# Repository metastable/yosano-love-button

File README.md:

# yosano-love-button
Field hack YOSANO - oryza -  ♥yosano button

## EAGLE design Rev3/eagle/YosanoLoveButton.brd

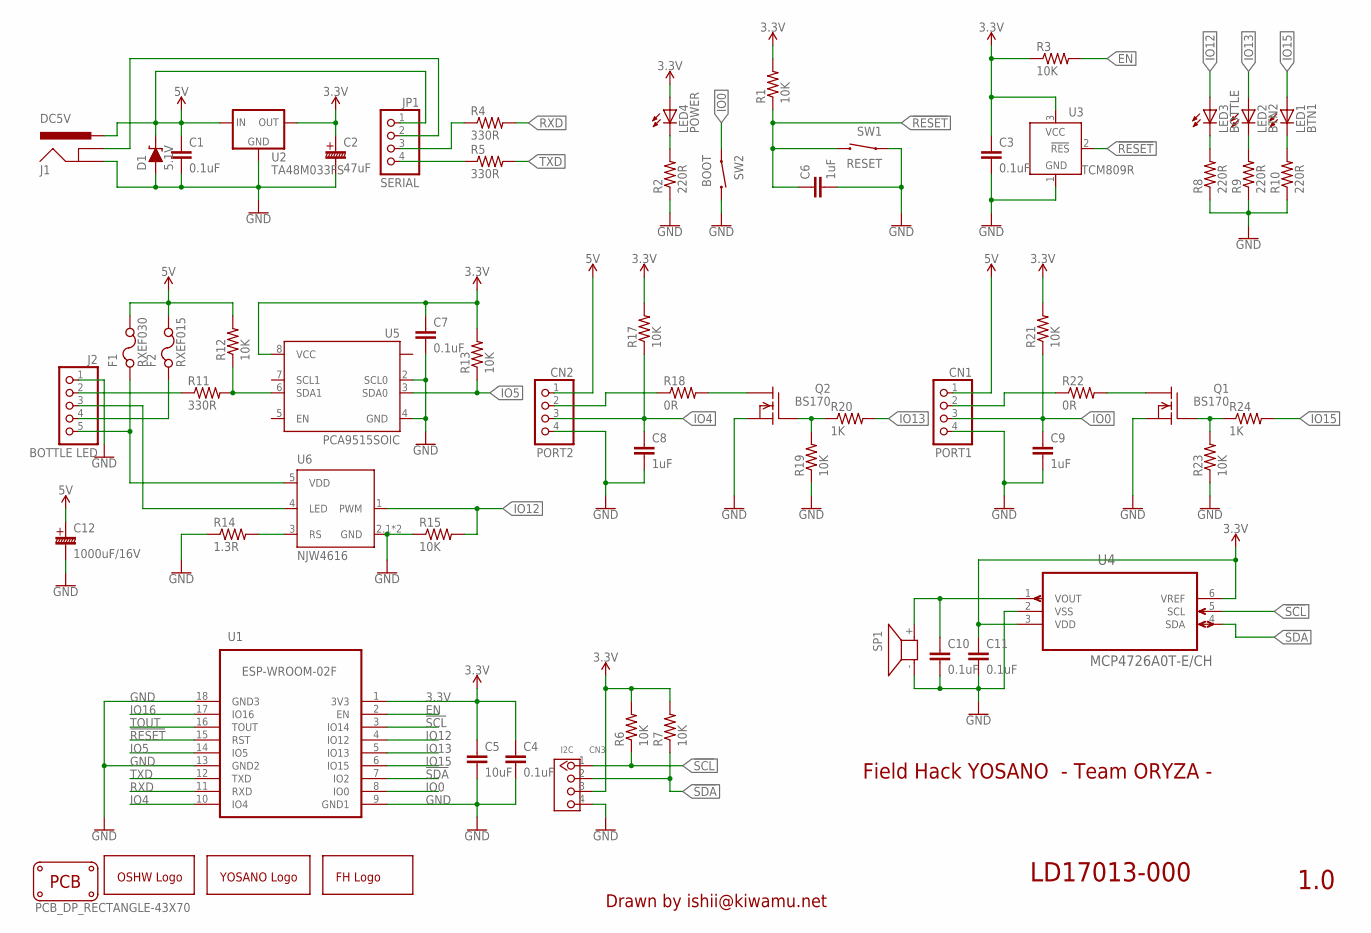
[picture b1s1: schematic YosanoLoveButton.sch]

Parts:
C1, C3, C4, C7: 0.1uF; C5B2.5
C2: 47uF; E2,0-5
C5: 10uF; C5B2.5
C6, C8, C9: 1uF; C5B2.5
C10, C11: 0.1uF; C5B2.5; MPN RDER72E104K2K1H03B
C12: 1000uF/16V; E5,0-10
CN1: PORT1; B4B-XH
CN2: PORT2; B4B-XH
CN3: I2C; HW4-2.0
D1: 5.1V; ZDIO-5-LD
F1: RXEF030; PTC-PTH
F2: RXEF015; PTC-PTH
GOLD_ORB_SM1: OSHWLOGOLOGO5MM; OSHW_5MM
J1: DC5V; POWER_JACK_PTH
J2: BOTTLE LED; MD-50SM
JP1: SERIAL; 1X04
LED1: BTN1; LED3MM
LED2: BTN2; LED3MM
LED3: BOTTLE; LED3MM
LED4: POWER; LED3MM
PCB1: PCB_DP_RECTANGLE-43X70; DP7043_V1
Q1, Q2: BS170; TO92
R1, R3, R6, R7, R12, R13, R15, R17, R19, R21, R23: 10K; 0204/5
R2, R8, R9, R10: 220R; 0204/5
R4, R5, R11: 330R; 0204/5
R14: 1.3R; 0204/5
R18, R22: 0R; 0204/5
R20, R24: 1K; 0204/5
SP1: PKM13EPYH4000
SW1: RESET; TVBP06
SW2: BOOT; TVBP06
U1: ESP-WROOM-02F; FRONT-FACE
U2: TA48M033FS; HSIP3
U3: TCM809R; SOT23B-3
U4: MCP4726A0T-E/CH; SOT95P270X145-6N
U5: PCA9515SOIC; SO08
U6: NJW4616; SOT-89-5
U$1: YOSANOLOGO; YOSANOCHO
U$2: FHLOGO; FIELDHACK-YOSANO

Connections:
3.3V: C2.+, C3.1, C4.1, C5.1, C7.1, C11.1, CN3.3, LED4.A, R1.2, R3.1, R6.2, R7.2, R13.2, R17.2, R21.2, U1.1 (3V3), U2.P$2 (OUT), U3.3 (VCC), U4.3 (VDD), U4.6 (VREF), U5.8 (VCC)
5V: C1.1, C12.+, CN1.1, CN2.1, D1.C, F1.2, F2.2, J1.PWR, JP1.1, R12.2, U2.P$1 (IN)
!RESET: C6.1, R1.1, SW1.2, U1.15 (RST), U3.2 (!RES)
!SCL: CN3.1, R6.1, U1.3 (IO14), U4.5 (SCL)
!SDA: CN3.2, R7.1, U1.7 (IO2), U4.4 (SDA)
EN: R3.2, U1.2 (EN)
GND: C1.2, C2.-, C3.2, C4.2, C5.2, C6.2, C7.2, C8.2, C9.2, C10.2, C11.2, C12.-, CN1.4, CN2.4, CN3.4, D1.A, J1.GND, J2.1, Q1.1 (S), Q2.1 (S), R2.1, R8.1, R9.1, R10.1, R14.1, R15.1, R19.1, R23.1, SP1.- (2), SW1.1, SW2.2, U1.9 (GND1), U1.13 (GND2), U1.18 (GND3), U2.P$3 (GND), U3.1 (GND), U4.2 (VSS), U5.2 (SCL0), U5.4 (GND), U6.2.1 (GND), U6.2.2 (GND)
IO0: C9.1, CN1.3, R21.1, SW2.1, U1.8 (IO0)
IO4: C8.1, CN2.3, R17.1, U1.10 (IO4)
IO5: R13.1, U1.14 (IO5), U5.3 (SDA0)
IO12: LED3.A, R15.2, U1.4 (IO12), U6.1 (PWM)
IO13: LED2.A, R20.2, U1.5 (IO13)
IO15: LED1.A, R24.2, U1.6 (IO15)
IO16: U1.17 (IO16)
unnamed: LED3.K (C), R8.2
unnamed: LED4.K (C), R2.2
unnamed: JP1.4, R5.1
unnamed: R14.2, U6.3 (RS)
unnamed: JP1.3, R4.1
unnamed: LED2.K (C), R9.2
unnamed: LED1.K (C), R10.2
unnamed: F1.1, J2.5, U6.5 (VDD)
unnamed: J2.3, U6.4 (LED)
unnamed: J1.GNDBREAK, JP1.2
unnamed: Q2.3 (D), R18.2
unnamed: J2.2, R11.1
unnamed: CN2.2, R18.1
unnamed: Q2.2 (G), R19.2, R20.1
unnamed: Q1.3 (D), R22.2
unnamed: C10.1, SP1.+ (1), U4.1 (VOUT)
unnamed: F2.1, J2.4
unnamed: Q1.2 (G), R23.2, R24.1
unnamed: CN1.2, R22.1
unnamed: R11.2, R12.1, U5.6 (SDA1)
RXD: R4.2, U1.11 (RXD)
TOUT: U1.16 (TOUT)
TXD: R5.2, U1.12 (TXD)

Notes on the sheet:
Field Hack YOSANO - Team ORYZA -
LD17013-000
Drawn by ishii@kiwamu.net
1.0

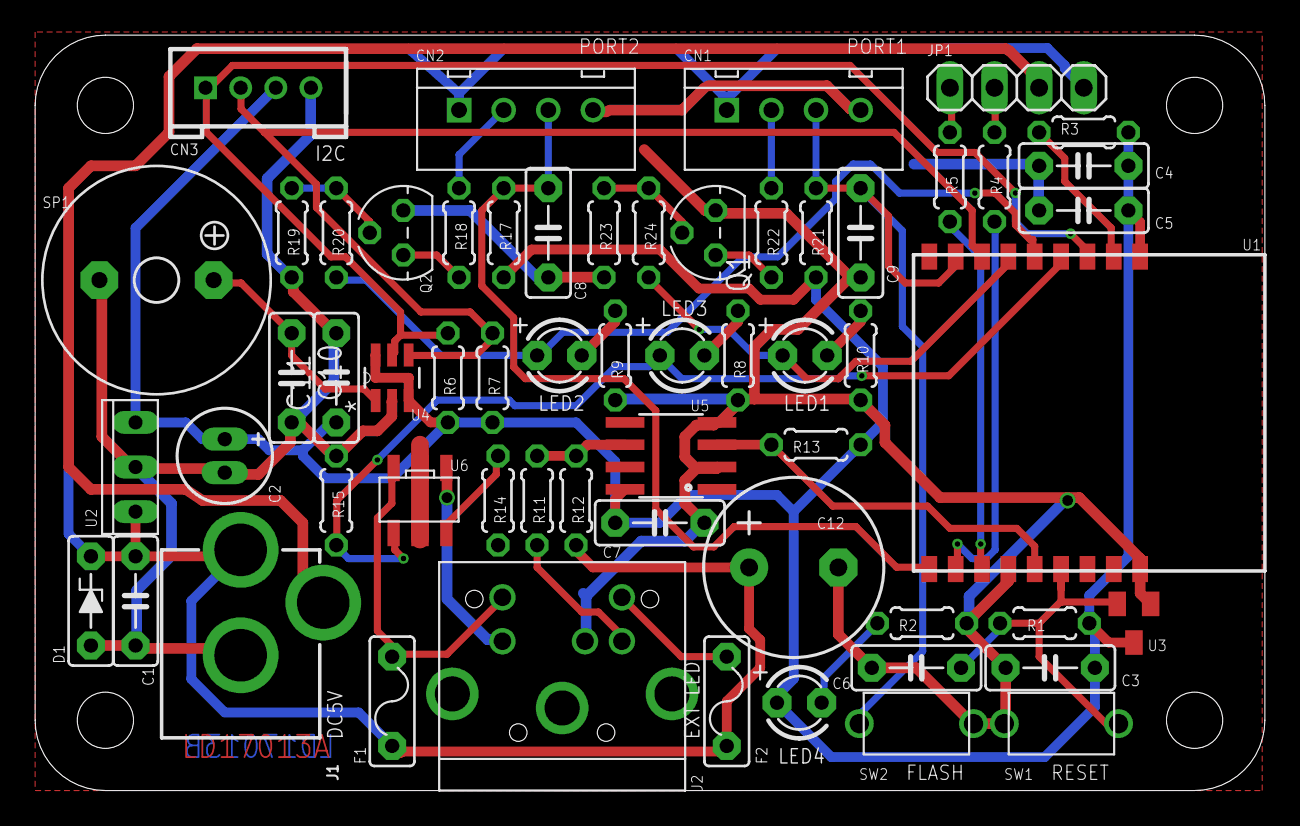
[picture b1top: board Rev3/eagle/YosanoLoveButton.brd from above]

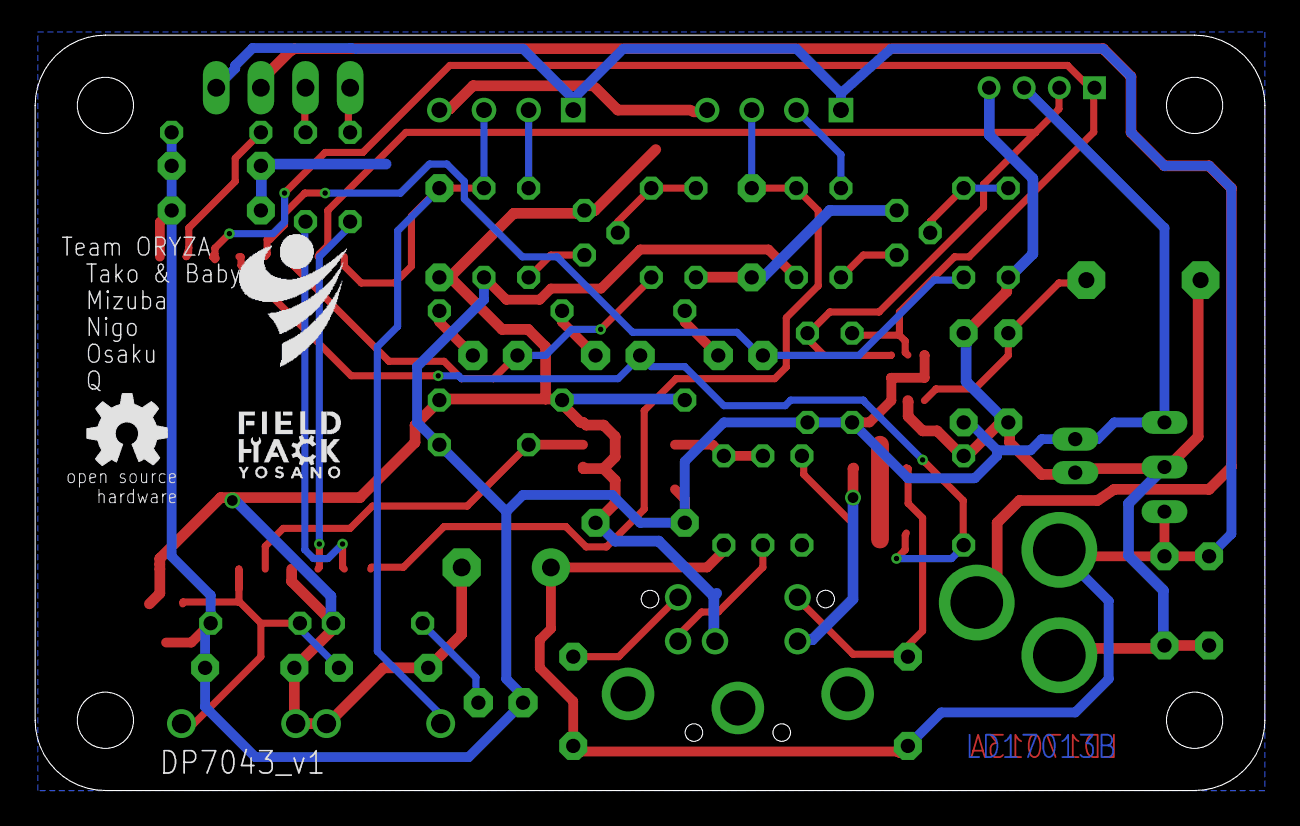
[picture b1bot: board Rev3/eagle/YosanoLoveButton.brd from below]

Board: 2 copper layers, 70.0 x 43.0 mm, 63 parts (3 on the bottom side), 35 nets.

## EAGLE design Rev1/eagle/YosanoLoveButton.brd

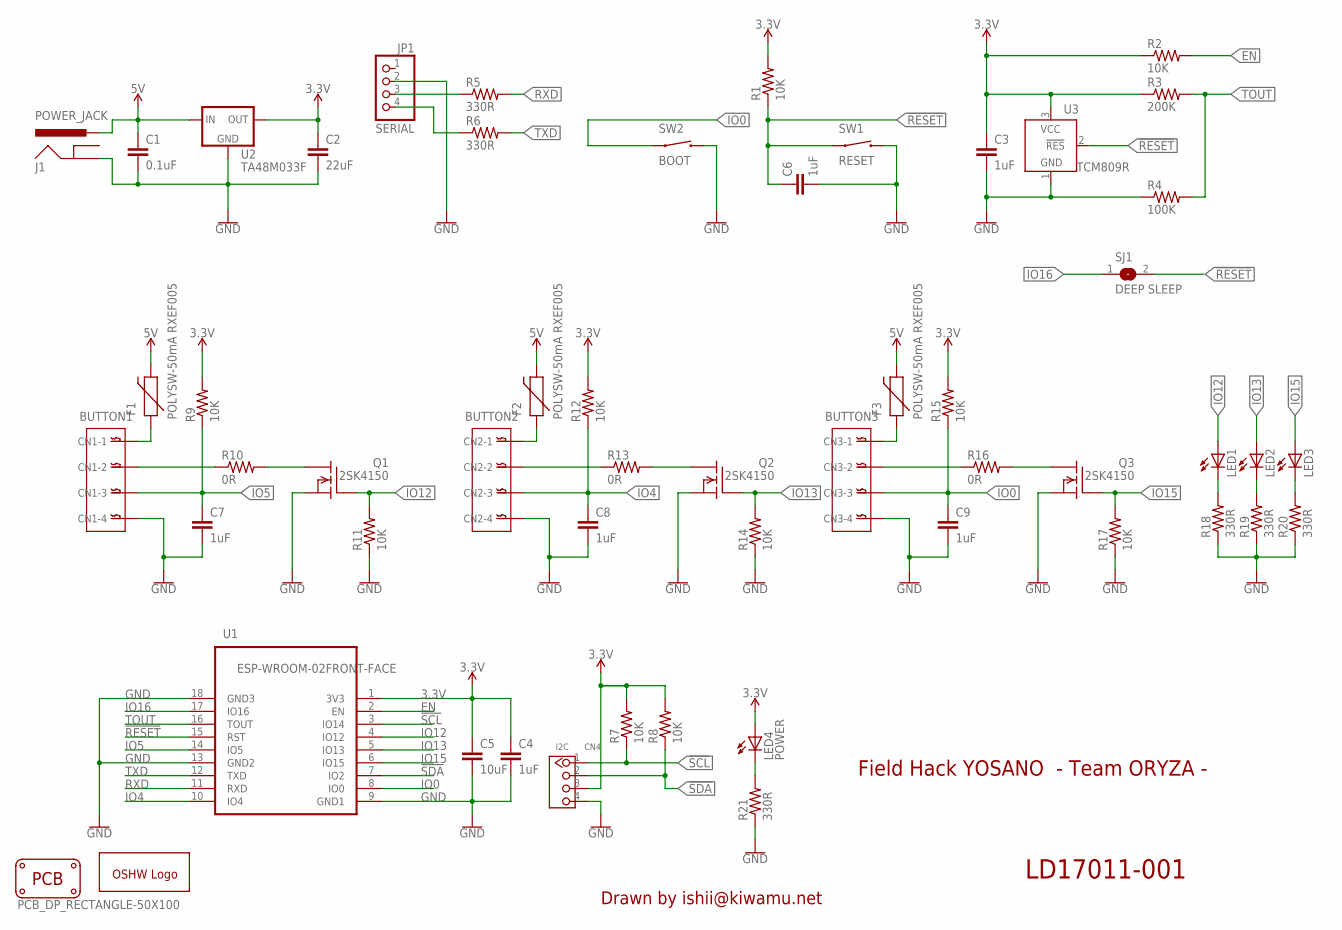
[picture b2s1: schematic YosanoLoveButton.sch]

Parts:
C1: 0.1uF; C5B2.5
C2: 22uF; C5B2.5
C3, C4, C6, C7, C8, C9: 1uF; C5B2.5
C5: 10uF; C5B2.5
CN1: BUTTON1; B4B-XH
CN2: BUTTON2; B4B-XH
CN3: BUTTON3; B4B-XH
CN4: I2C; HW4-2.0
F1, F2, F3: POLYSW-50mA RXEF005; PTC
GOLD_ORB_SM1: OSHWLOGOLOGO5MM; OSHW_5MM
J1: POWER_JACK; POWER_JACK_PTH
JP1: SERIAL; 1X04
LED1, LED2, LED3: LED3MM
LED4: POWER; LED3MM
PCB1: PCB_DP_RECTANGLE-50X100; DP10050_V1
Q1, Q2, Q3: 2SK4150; TO92
R1, R2, R7, R8, R9, R11, R12, R14, R15, R17: 10K; 0204/7
R3: 200K; 0204/7
R4: 100K; 0204/7
R5, R6, R18, R19, R20, R21: 330R; 0204/7
R10, R13, R16: 0R; 0204/7
SJ1: DEEP SLEEP; SOLDERJUMPER_REFLOW
SW1: RESET; TVBP06
SW2: BOOT; TVBP06
U1: ESP-WROOM-02FRONT-FACE; FRONT-FACE
U2: TA48M033F; DPACK
U3: TCM809R; SOT23B-3

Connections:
3.3V: C2.1, C3.1, C4.1, C5.1, CN4.3, LED4.A, R1.2, R2.1, R3.1, R7.2, R8.2, R9.2, R12.2, R15.2, U1.1 (3V3), U2.3 (OUT), U3.3 (VCC)
5V: C1.1, F1.P$2 (2), F2.P$2 (2), F3.P$2 (2), J1.PWR, U2.1 (IN)
!RESET: C6.1, R1.1, SJ1.2, SW1.1, U1.15 (RST), U3.2 (!RES)
!SCL: CN4.1, R7.1, U1.3 (IO14)
!SDA: CN4.2, R8.1, U1.7 (IO2)
EN: R2.2, U1.2 (EN)
GND: C1.2, C2.2, C3.2, C4.2, C5.2, C6.2, C7.2, C8.2, C9.2, CN1.P$4, CN2.P$4, CN3.P$4, CN4.4, J1.GND, JP1.2, Q1.1 (S), Q2.1 (S), Q3.1 (S), R4.1, R11.1, R14.1, R17.1, R18.1, R19.1, R20.1, R21.1, SW1.2, SW2.2, U1.9 (GND1), U1.13 (GND2), U1.18 (GND3), U2.4 (GND), U3.1 (GND)
IO0: C9.1, CN3.P$3, R15.1, SW2.1, U1.8 (IO0)
IO4: C8.1, CN2.P$3, R12.1, U1.10 (IO4)
IO5: C7.1, CN1.P$3, R9.1, U1.14 (IO5)
IO12: LED1.A, Q1.2 (G), R11.2, U1.4 (IO12)
IO13: LED2.A, Q2.2 (G), R14.2, U1.5 (IO13)
IO15: LED3.A, Q3.2 (G), R17.2, U1.6 (IO15)
IO16: SJ1.1, U1.17 (IO16)
unnamed: LED1.K (C), R18.2
unnamed: LED4.K (C), R21.2
unnamed: JP1.4, R6.1
unnamed: Q1.3 (D), R10.2
unnamed: JP1.3, R5.1
unnamed: LED2.K (C), R19.2
unnamed: LED3.K (C), R20.2
unnamed: CN1.P$1, F1.P$1 (1)
unnamed: CN1.P$2, R10.1
unnamed: Q2.3 (D), R13.2
unnamed: CN2.P$1, F2.P$1 (1)
unnamed: CN2.P$2, R13.1
unnamed: Q3.3 (D), R16.2
unnamed: CN3.P$1, F3.P$1 (1)
unnamed: CN3.P$2, R16.1
RXD: R5.2, U1.11 (RXD)
TOUT: R3.2, R4.2, U1.16 (TOUT)
TXD: R6.2, U1.12 (TXD)

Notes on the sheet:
Field Hack YOSANO - Team ORYZA -
LD17011-001
Drawn by ishii@kiwamu.net

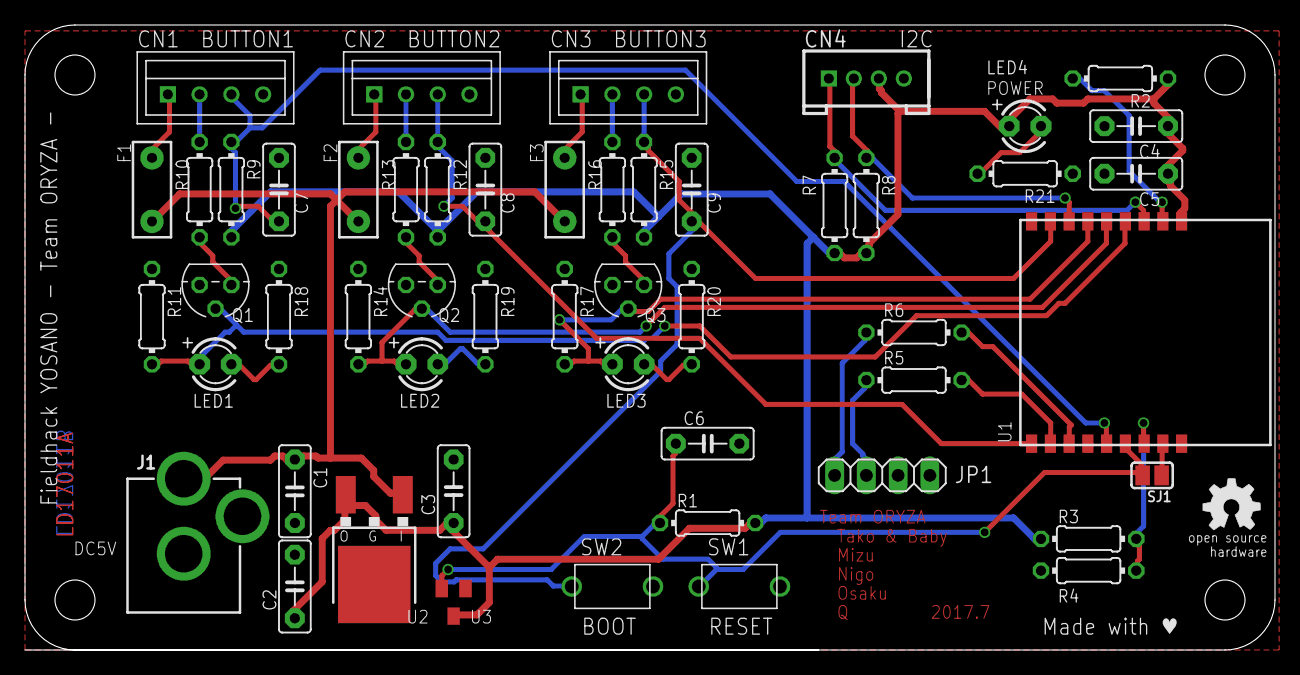
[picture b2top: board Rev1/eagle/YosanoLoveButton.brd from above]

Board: 2 copper layers, 100.0 x 50.0 mm, 54 parts (0 on the bottom side), 32 nets.

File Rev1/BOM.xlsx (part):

Part | Value | Device | Package | Description | 名前ナマエ | MF | MPN | OC_AKIZUKI | OC_SENGOKU | OC_MARUTSU | 単価タンカ
C1 | 0.1uF | C5/2.5 | C5B2.5 | CAPACITOR | 絶縁ラジアルリード型積層セラミックコンデンサー０．１μＦ５０Ｖ５ｍｍ（１０個入） | 株式会社村田製作所(muRata) | RPEF11H104Z2K1A01B | P-02211 |  |  | 10
C2 | 22uF | C5/2.5 | C5B2.5 | CAPACITOR | 絶縁ラジアルリード型積層セラミックコンデンサ ２２μＦ５０Ｖ５ｍｍ | 株式会社村田製作所(muRata) | RDEC71H226MWK1H03B | P-08156 |  |  | 80
C3 | 1uF | C5/2.5 | C5B2.5 | CAPACITOR | 絶縁ラジアルリード型積層セラミックコンデンサ １μＦ５０Ｖ５ｍｍ | 株式会社村田製作所(muRata) | RDER71H105K2K1H03B | P-08150 |  |  | 20
C4 | 1uF | C5/2.5 | C5B2.5 | CAPACITOR | 絶縁ラジアルリード型積層セラミックコンデンサ １μＦ５０Ｖ５ｍｍ | 株式会社村田製作所(muRata) | RDER71H105K2K1H03B | P-08150 |  |  | 20
C5 | 10uF | C5/2.5 | C5B2.5 | CAPACITOR | 絶縁ラジアルリード型積層セラミックコンデンサ １０μＦ５０Ｖ５ｍｍ | 株式会社村田製作所(muRata) | RDEC71H106K3K1H03B | P-08155 |  |  | 50
C6 | 1uF | C5/2.5 | C5B2.5 | CAPACITOR | 絶縁ラジアルリード型積層セラミックコンデンサ １μＦ５０Ｖ５ｍｍ | 株式会社村田製作所(muRata) | RDER71H105K2K1H03B | P-08150 |  |  | 20
C7 | 1uF | C5/2.5 | C5B2.5 | CAPACITOR | 絶縁ラジアルリード型積層セラミックコンデンサ １μＦ５０Ｖ５ｍｍ | 株式会社村田製作所(muRata) | RDER71H105K2K1H03B | P-08150 |  |  | 20
C8 | 1uF | C5/2.5 | C5B2.5 | CAPACITOR | 絶縁ラジアルリード型積層セラミックコンデンサ １μＦ５０Ｖ５ｍｍ | 株式会社村田製作所(muRata) | RDER71H105K2K1H03B | P-08150 |  |  | 20
C9 | 1uF | C5/2.5 | C5B2.5 | CAPACITOR | 絶縁ラジアルリード型積層セラミックコンデンサ １μＦ５０Ｖ５ｍｍ | 株式会社村田製作所(muRata) | RDER71H105K2K1H03B | P-08150 |  |  | 20
CN1 | BUTTON1 | 04-JST-B4B-XH-A | B4B-XH | JST CONNECTOR | XHコネクタ 基板用ポスト 4P ストレート | 日本圧着端子製造(JST) | B4B-XH-A(LF)(SN) |  |  |  | 42
CN2 | BUTTON2 | 04-JST-B4B-XH-A | B4B-XH | JST CONNECTOR | XHコネクタ 基板用ポスト 4P ストレート | 日本圧着端子製造(JST) | B4B-XH-A(LF)(SN) |  |  |  | 42
CN3 | BUTTON3 | 04-JST-B4B-XH-A | B4B-XH | JST CONNECTOR | XHコネクタ 基板用ポスト 4P ストレート | 日本圧着端子製造(JST) | B4B-XH-A(LF)(SN) |  |  |  | 42
CN4 | I2C | GROVE-CONNECTOR-DIP(4P-2.0) | HW4-2.0 | Grove Connector | Grove用-4ピンコネクタ ストレート(オス)10個入り | Seeed Studio | 110990030 |  |  |  | 10
F1 | POLYSW-50mA RXEF005 | PTCPTH | PTC | Resettable Fuse PTC | ポリスイッチ５０ｍＡ（１００ｍＡで遮断） 耐圧：６０Ｖ ＲＸＥＦ００５ | Littelfuse, Inc./Tyco Electronics Corporation/Raychem | RXEF005 | P-01352 |  |  | 30
F2 | POLYSW-50mA RXEF005 | PTCPTH | PTC | Resettable Fuse PTC | ポリスイッチ５０ｍＡ（１００ｍＡで遮断） 耐圧：６０Ｖ ＲＸＥＦ００５ | Littelfuse, Inc./Tyco Electronics Corporation/Raychem | RXEF005 | P-01352 |  |  | 30
F3 | POLYSW-50mA RXEF005 | PTCPTH | PTC | Resettable Fuse PTC | ポリスイッチ５０ｍＡ（１００ｍＡで遮断） 耐圧：６０Ｖ ＲＸＥＦ００５ | Littelfuse, Inc./Tyco Electronics Corporation/Raychem | RXEF005 | P-01352 |  |  | 30
J1 | DC5V | POWER_JACK | POWER_JACK_PTH | Power Jack Connector | ２．１ｍｍ標準ＤＣジャック 基板取付用 ＭＪ－１７９Ｐ | マル信無線電機株式会社 | MJ-179P | C-00077 |  |  | 40
JP1 | SERIAL | PINHD-1X4 | 1X04 | PIN HEADER | 細ピンヘッダ １×４ | Useconn Electronics Ltd. | PHA-1x4SG | C-04392 |  |  | 5
LED1 |  | LED3MM | LED3MM | LED | ３ｍｍ赤色ＬＥＤ ７０° ＯＳＲ５ＪＡ３Ｚ７４Ａ | OptoSupply | OSR5JA3Z74A | I-11577 |  |  | 10
LED2 |  | LED3MM | LED3MM | LED | ３ｍｍ赤色ＬＥＤ ７０° ＯＳＲ５ＪＡ３Ｚ７４Ａ | OptoSupply | OSR5JA3Z74A | I-11577 |  |  | 10
LED3 |  | LED3MM | LED3MM | LED | ３ｍｍ赤色ＬＥＤ ７０° ＯＳＲ５ＪＡ３Ｚ７４Ａ | OptoSupply | OSR5JA3Z74A | I-11577 |  |  | 10
LED4 | POWER | LED3MM | LED3MM | LED | ３ｍｍ赤色ＬＥＤ ７０° ＯＳＲ５ＪＡ３Ｚ７４Ａ | OptoSupply | OSR5JA3Z74A | I-11577 |  |  | 10
Q1 | 2SK4150 | BSS101 | TO92 | N-Channel Enhancement MOSFET 200V 0,16A 11Ohm | Ｎｃｈ ＭＯＳＦＥＴ ２ＳＫ４１５０ＴＺ－Ｅ （２５０Ｖ０．４Ａ）（１０個入） | ルネサスエレクトロニクス株式会社(Renesas) | 2SK4150TZ-E | I-09027 |  |  | 25
Q2 | 2SK4150 | BSS101 | TO92 | N-Channel Enhancement MOSFET 200V 0,16A 11Ohm | Ｎｃｈ ＭＯＳＦＥＴ ２ＳＫ４１５０ＴＺ－Ｅ （２５０Ｖ０．４Ａ）（１０個入） | ルネサスエレクトロニクス株式会社(Renesas) | 2SK4150TZ-E | I-09027 |  |  | 25
Q3 | 2SK4150 | BSS101 | TO92 | N-Channel Enhancement MOSFET 200V 0,16A 11Ohm | Ｎｃｈ ＭＯＳＦＥＴ ２ＳＫ４１５０ＴＺ－Ｅ （２５０Ｖ０．４Ａ）（１０個入） | ルネサスエレクトロニクス株式会社(Renesas) | 2SK4150TZ-E | I-09027 |  |  | 25
R1 | 10K | R-US_0204/7 | 0204/7 | RESISTOR, American symbol | カーボン抵抗（炭素皮膜抵抗） １／４Ｗ １０ｋΩ （１００本入） | SHIH HAO Electronics CO.,LTD | RD25S 10K | R-25103 |  |  | 1
R2 | 10K | R-US_0204/7 | 0204/7 | RESISTOR, American symbol | カーボン抵抗（炭素皮膜抵抗） １／４Ｗ １０ｋΩ （１００本入） | SHIH HAO Electronics CO.,LTD | RD25S 10K | R-25103 |  |  | 1
R3 | 200K | R-US_0204/7 | 0204/7 | RESISTOR, American symbol | カーボン抵抗（炭素皮膜抵抗） １／４Ｗ ２００ｋΩ （１００本入） | SHIH HAO Electronics CO.,LTD | RD25S 200K | R-25204 |  |  | 1
R4 | 100K | R-US_0204/7 | 0204/7 | RESISTOR, American symbol | カーボン抵抗（炭素皮膜抵抗） １／４Ｗ １００ｋΩ （１００本入） | SHIH HAO Electronics CO.,LTD | RD25S 100K | R-25104 |  |  | 1
R5 | 330R | R-US_0204/7 | 0204/7 | RESISTOR, American symbol | カーボン抵抗（炭素皮膜抵抗） １／４Ｗ ３３０Ω （１００本入） | FAITHFUL LINK INDUSTRIAL CORP. | CF25J330RB | R-25331 |  |  | 1
R6 | 330R | R-US_0204/7 | 0204/7 | RESISTOR, American symbol | カーボン抵抗（炭素皮膜抵抗） １／４Ｗ ３３０Ω （１００本入） | FAITHFUL LINK INDUSTRIAL CORP. | CF25J330RB | R-25331 |  |  | 1
R7 | 10K | R-US_0204/7 | 0204/7 | RESISTOR, American symbol | カーボン抵抗（炭素皮膜抵抗） １／４Ｗ １０ｋΩ （１００本入） | SHIH HAO Electronics CO.,LTD | RD25S 10K | R-25103 |  |  | 1
R8 | 10K | R-US_0204/7 | 0204/7 | RESISTOR, American symbol | カーボン抵抗（炭素皮膜抵抗） １／４Ｗ １０ｋΩ （１００本入） | SHIH HAO Electronics CO.,LTD | RD25S 10K | R-25103 |  |  | 1
R9 | 10K | R-US_0204/7 | 0204/7 | RESISTOR, American symbol | カーボン抵抗（炭素皮膜抵抗） １／４Ｗ １０ｋΩ （１００本入） | SHIH HAO Electronics CO.,LTD | RD25S 10K | R-25103 |  |  | 1
R10 | 0R | R-US_0204/7 | 0204/7 | RESISTOR, American symbol | カーボン抵抗（炭素皮膜抵抗） １／４Ｗ ０Ω （１００本入） | SHIH HAO Electronics CO.,LTD | RD25S 0E | R-25000 |  |  | 1
R11 | 10K | R-US_0204/7 | 0204/7 | RESISTOR, American symbol | カーボン抵抗（炭素皮膜抵抗） １／４Ｗ １０ｋΩ （１００本入） | SHIH HAO Electronics CO.,LTD | RD25S 10K | R-25103 |  |  | 1
R12 | 10K | R-US_0204/7 | 0204/7 | RESISTOR, American symbol | カーボン抵抗（炭素皮膜抵抗） １／４Ｗ １０ｋΩ （１００本入） | SHIH HAO Electronics CO.,LTD | RD25S 10K | R-25103 |  |  | 1
R13 | 0R | R-US_0204/7 | 0204/7 | RESISTOR, American symbol | カーボン抵抗（炭素皮膜抵抗） １／４Ｗ ０Ω （１００本入） | SHIH HAO Electronics CO.,LTD | RD25S 0E | R-25000 |  |  | 1
R14 | 10K | R-US_0204/7 | 0204/7 | RESISTOR, American symbol | カーボン抵抗（炭素皮膜抵抗） １／４Ｗ １０ｋΩ （１００本入） | SHIH HAO Electronics CO.,LTD | RD25S 10K | R-25103 |  |  | 1
R15 | 10K | R-US_0204/7 | 0204/7 | RESISTOR, American symbol | カーボン抵抗（炭素皮膜抵抗） １／４Ｗ １０ｋΩ （１００本入） | SHIH HAO Electronics CO.,LTD | RD25S 10K | R-25103 |  |  | 1
R16 | 0R | R-US_0204/7 | 0204/7 | RESISTOR, American symbol | カーボン抵抗（炭素皮膜抵抗） １／４Ｗ ０Ω （１００本入） | SHIH HAO Electronics CO.,LTD | RD25S 0E | R-25000 |  |  | 1
R17 | 10K | R-US_0204/7 | 0204/7 | RESISTOR, American symbol | カーボン抵抗（炭素皮膜抵抗） １／４Ｗ １０ｋΩ （１００本入） | SHIH HAO Electronics CO.,LTD | RD25S 10K | R-25103 |  |  | 1
R18 | 330R | R-US_0204/7 | 0204/7 | RESISTOR, American symbol | カーボン抵抗（炭素皮膜抵抗） １／４Ｗ ３３０Ω （１００本入） | FAITHFUL LINK INDUSTRIAL CORP. | CF25J330RB | R-25331 |  |  | 1
R19 | 330R | R-US_0204/7 | 0204/7 | RESISTOR, American symbol | カーボン抵抗（炭素皮膜抵抗） １／４Ｗ ３３０Ω （１００本入） | FAITHFUL LINK INDUSTRIAL CORP. | CF25J330RB | R-25331 |  |  | 1
R20 | 330R | R-US_0204/7 | 0204/7 | RESISTOR, American symbol | カーボン抵抗（炭素皮膜抵抗） １／４Ｗ ３３０Ω （１００本入） | FAITHFUL LINK INDUSTRIAL CORP. | CF25J330RB | R-25331 |  |  | 1
R21 | 330R | R-US_0204/7 | 0204/7 | RESISTOR, American symbol | カーボン抵抗（炭素皮膜抵抗） １／４Ｗ ３３０Ω （１００本入） | FAITHFUL LINK INDUSTRIAL CORP. | CF25J330RB | R-25331 |  |  | 1
SW1 | RESET | TVBP06 | TVBP06 | 2pin switch. | タクトスイッチ（黒） | Zhejiang Jianfu Electronics Co., Ltd | TVBP06-B043CB-B | P-08073 |  |  | 20
SW2 | BOOT | TVBP06 | TVBP06 | 2pin switch. | タクトスイッチ（黒） | Zhejiang Jianfu Electronics Co., Ltd | TVBP06-B043CB-B | P-08073 |  |  | 20
U1 | ESP-WROOM-02FRONT-FACE | ESP-WROOM-02FRONT-FACE | FRONT-FACE | WiFi module - ESP-WROOM-02 | Ｗｉ－Ｆｉモジュール ＥＳＰ－ＷＲＯＯＭ－０２ | Espressif Systems (Shanghai) Pte. Ltd. | ESP-WROOM-02 | M-09607 |  |  | 550
U2 | TA48M033F | TA48M033F | DPACK | TA48 series | 低損失三端子レギュレーター ３．３Ｖ５００ｍＡ ＴＡ４８Ｍ０３３Ｆ（Ｓ Ｑ） | 株式会社東芝セミコンダクター社(TOSHIBA) | TA48M033F(S Q) | I-00538 |  |  | 100
U3 | TCM809R | TCM809 | SOT23B-3 | POWER SUPPLY MONITOR | リセットＩＣ ＴＣＭ８０９Ｒ（８個入） | Microchip Technology Inc.(マイクロチップ) | TCM809RVNB | I-02533 |  |  | 25
GOLD_ORB_SM1 | OSHWLOGOLOGO5MM | OSHWLOGOLOGO5MM | OSHW_5MM | The OSHW logo for PCB layout |  |  |  |  |  |  | 0
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
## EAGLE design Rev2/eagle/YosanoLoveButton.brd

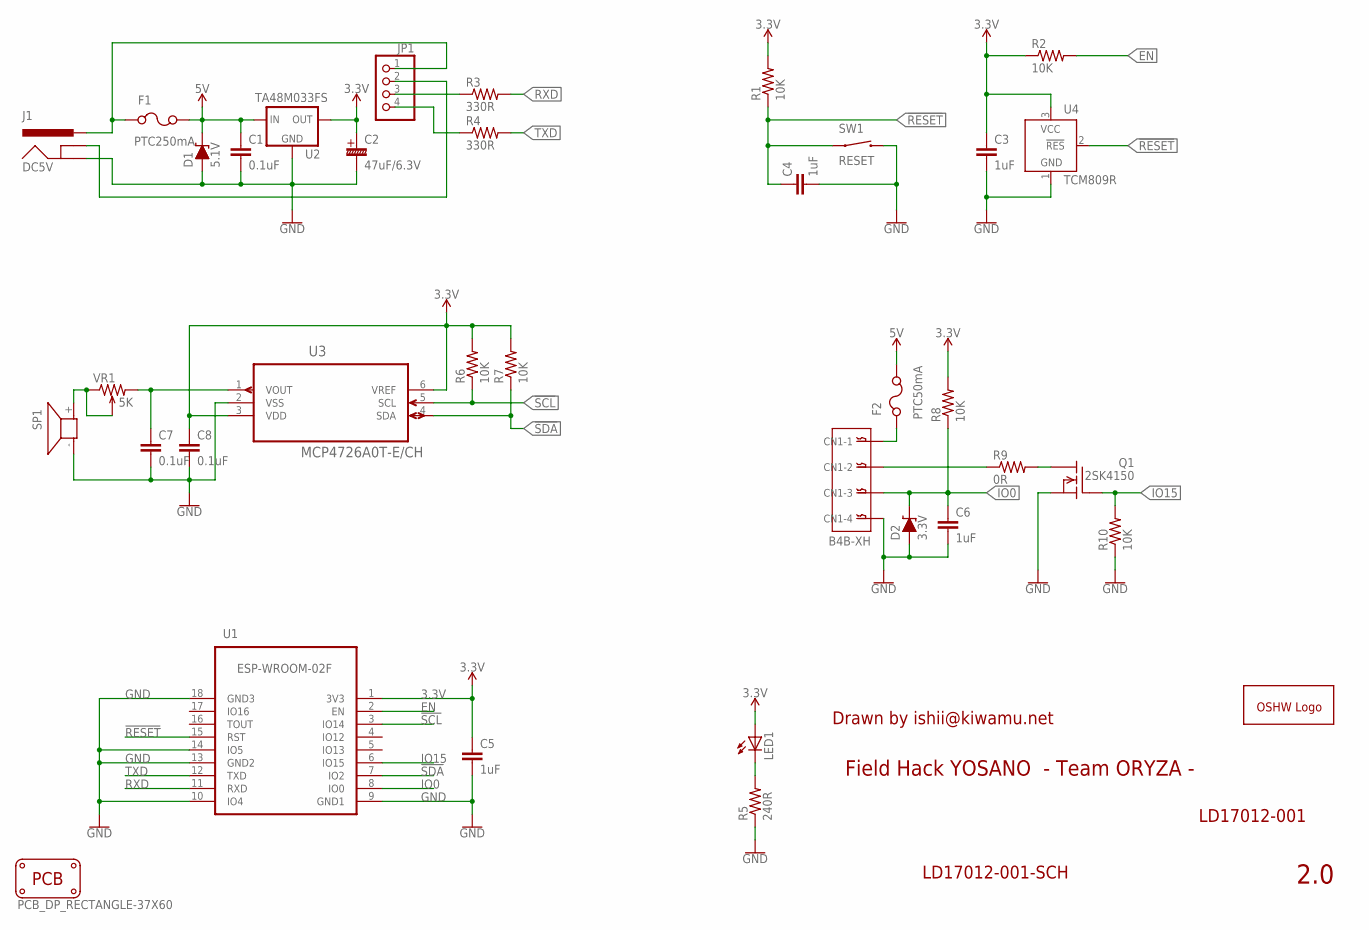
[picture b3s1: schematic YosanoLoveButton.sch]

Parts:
C1, C7, C8: 0.1uF; C5B2.5; MPN RDER72E104K2K1H03B
C2: 47uF/6.3V; E2,0-5; MPN 0JUTCX470M
C3, C4, C5, C6: 1uF; C5B2.5; MPN RDER71H105K2K1H03B
CN1: B4B-XH
D1: 5.1V; ZDIO-5-LD; MPN GDZJ5.1B
D2: 3.3V; ZDIO-5-LD; MPN GDZJ3.3B
F1: PTC250mA; PTC-PTH; MPN RXEF005
F2: PTC50mA; PTC-PTH; MPN RXEF005
GOLD_ORB_SM1: OSHWLOGOLOGO5MM; OSHW_5MM
J1: DC5V; POWER_JACK_PTH
JP1: PINHD-1X4; 1X04
LED1: LED3MM; MPN OSR5JA3Z74A
PCB1: PCB_DP_RECTANGLE-37X60; DP6037_V1
Q1: 2SK4150; TO92
R1, R2, R6, R7, R8, R10: 10K; 0204/5; MPN RD25SJ10K
R3: 330R; 0204/5; MPN RD25SJ330R
R4: 330R; 0204/5; MPN RD25SJ300R
R5: 240R; 0204/5; MPN RD25SJ 240R
R9: 0R; 0204/5; MPN RD25SP 0R
SP1: PKM13EPYH4000
SW1: RESET; TVBP06
U1: ESP-WROOM-02F; FRONT-FACE
U2: TA48M033FS; HSIP3
U3: MCP4726A0T-E/CH; SOT95P270X145-6N
U4: TCM809R; SOT23B-3
VR1: 5K; 3362P

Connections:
3.3V: C2.+, C3.1, C5.1, C8.1, LED1.A, R1.2, R2.1, R6.2, R7.2, R8.2, U1.1 (3V3), U2.P$2 (OUT), U3.3 (VDD), U3.6 (VREF), U4.3 (VCC)
5V: C1.1, D1.C, F1.2, F2.2, U2.P$1 (IN)
!RESET: C4.1, R1.1, SW1.1, U1.15 (RST), U4.2 (!RES)
!SCL: R6.1, U1.3 (IO14), U3.5 (SCL)
!SDA: R7.1, U1.7 (IO2), U3.4 (SDA)
EN: R2.2, U1.2 (EN)
GND: C1.2, C2.-, C3.2, C4.2, C5.2, C6.2, C7.2, C8.2, CN1.P$4, D1.A, D2.A, J1.GND, Q1.1 (S), R5.1, R10.1, SP1.- (2), SW1.2, U1.9 (GND1), U1.10 (IO4), U1.13 (GND2), U1.14 (IO5), U1.18 (GND3), U2.P$3 (GND), U3.2 (VSS), U4.1 (GND)
IO0: C6.1, CN1.P$3, D2.C, R8.1, U1.8 (IO0)
IO15: Q1.2 (G), R10.2, U1.6 (IO15)
unnamed: F1.1, J1.PWR, JP1.1
unnamed: LED1.K (C), R5.2
unnamed: JP1.4, R4.1
unnamed: C7.1, U3.1 (VOUT), VR1.3
unnamed: JP1.3, R3.1
unnamed: SP1.+ (1), VR1.1, VR1.2
unnamed: J1.GNDBREAK, JP1.2
unnamed: Q1.3 (D), R9.2
unnamed: CN1.P$1, F2.1
unnamed: CN1.P$2, R9.1
RXD: R3.2, U1.11 (RXD)
TXD: R4.2, U1.12 (TXD)

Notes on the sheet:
Field Hack YOSANO - Team ORYZA -
LD17012-001
Drawn by ishii@kiwamu.net
2.0
LD17012-001-SCH

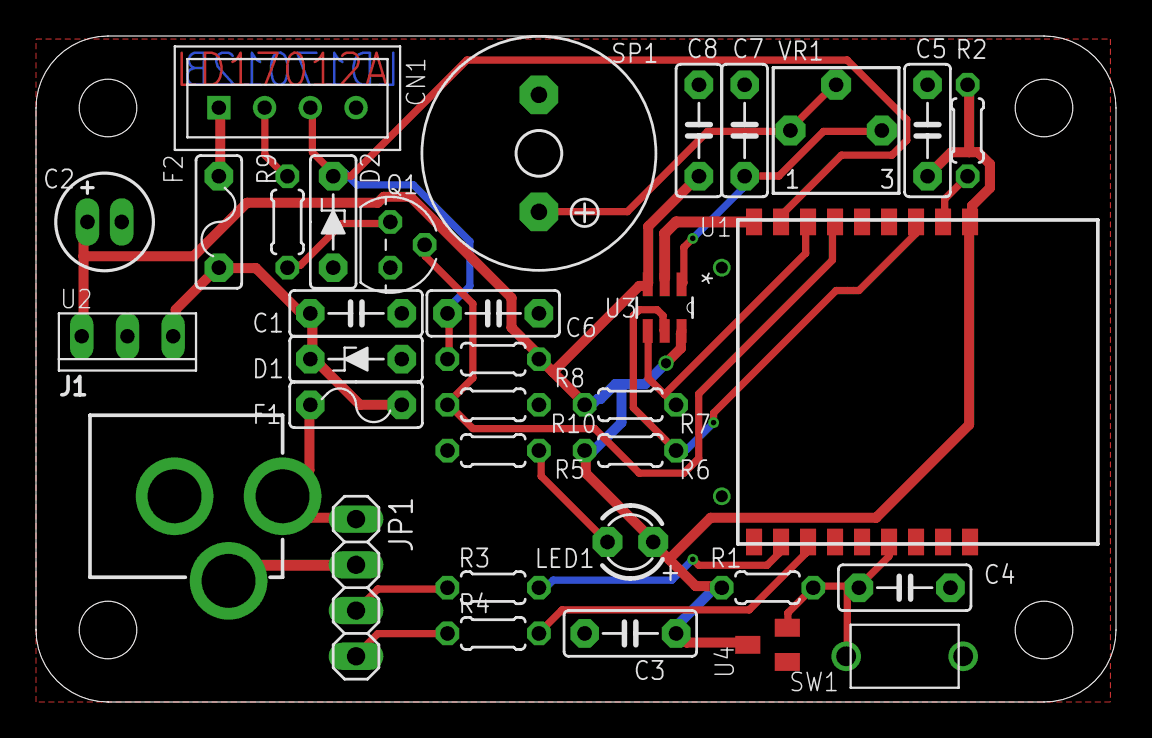
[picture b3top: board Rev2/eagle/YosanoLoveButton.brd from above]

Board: 2 copper layers, 60.0 x 37.0 mm, 36 parts (1 on the bottom side), 21 nets.

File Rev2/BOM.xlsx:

Part | Value | Device | Package | Description | COLOR | SPEC | MF | MPN | OC_AKIZUKI | OC_SENGOKU | OC_SWITCHSCIENCE | OC_MARUTSU | PACKAGE2 | 単価タンカ
C1 | 0.1uF | C5/2.5 | C5B2.5 | CAPACITOR |  | 104 | 株式会社村田製作所(muRata) | RDER72E104K2K1H03B | P-10147 |  |  |  |  | 15
C2 | 47uF/6.3V | C-PR-2,0X5 | E2,0-5 | POLARIZED ELECTROLYTIC/TANTALUM |  | 470 | 東信工業 | 0JUTCX470M |  | 6548-54KH |  |  |  | 21
C3 | 1uF | C5/2.5 | C5B2.5 | CAPACITOR |  | 105 | 株式会社村田製作所(muRata) | RDER71H105K2K1H03B | P-08150 |  |  |  |  | 20
C4 | 1uF | C5/2.5 | C5B2.5 | CAPACITOR |  | 105 | 株式会社村田製作所(muRata) | RDER71H105K2K1H03B | P-08150 |  |  |  |  | 20
C5 | 1uF | C5/2.5 | C5B2.5 | CAPACITOR |  | 105 | 株式会社村田製作所(muRata) | RDER71H105K2K1H03B | P-08150 |  |  |  |  | 20
C6 | 1uF | C5/2.5 | C5B2.5 | CAPACITOR |  | 105 | 株式会社村田製作所(muRata) | RDER71H105K2K1H03B | P-08150 |  |  |  |  | 20
C7 | 0.1uF | C5/2.5 | C5B2.5 | CAPACITOR |  | 104 | 株式会社村田製作所(muRata) | RDER72E104K2K1H03B | P-10147 |  |  |  |  | 15
C8 | 0.1uF | C5/2.5 | C5B2.5 | CAPACITOR |  | 104 | 株式会社村田製作所(muRata) | RDER72E104K2K1H03B | P-10147 |  |  |  |  | 15
CN1 | B4B-XH | 04-JST-B4B-XH-A | B4B-XH | JST CONNECTOR |  |  | 日本圧着端子製造(JST) | B4B-XH-A(LF)(SN) |  | 5AL6-8BMK |  |  |  | 42
D1 | 5.1V | ZENER-DIODEZD-5LD | ZDIO-5-LD | Z-Diode |  |  | PANJIT | GDZJ5.1B | I-07493 |  |  |  |  | 10
D2 | 3.3V | ZENER-DIODEZD-5LD | ZDIO-5-LD | Z-Diode |  |  | PANJIT | GDZJ3.3B | I-07491 |  |  |  |  | 10
F1 | PTC250mA | PTCPTH | PTC-PTH | Resettable Fuse PTC |  |  | Tyco Electronics Corporation | RXEF025 | P-01354 |  |  |  |  | 30
F2 | PTC50mA | PTCPTH | PTC-PTH | Resettable Fuse PTC |  |  | Tyco Electronics Corporation | RXEF005 | P-01352 |  |  |  |  | 30
J1 | DC5V | POWER_JACK | POWER_JACK_PTH | Power Jack Connector |  |  | マル信無線電機株式会社 | MJ-179P | C-00077 |  |  |  |  | 40
JP1 |  | PINHD-1X4 | 1X04 | PIN HEADER |  |  | Useconn Electronics Ltd. | PHA-1x4SG | C-04392 |  |  |  |  | 5
LED1 |  | LED3MM | LED3MM | LED | 赤アカ |  | OptoSupply | OSR5JA3Z74A | I-11577 |  |  |  |  | 10
Q1 | 2SK4150 | 2SK4150 | TO92 | Silicon N Channel MOS FET High Speed Power Switching 250V 0.4A TO-92 |  | 2SK4150 | RENESAS | 2SK4150TZ-E | I-09027 |  |  |  | TO-92 | 25
R1 | 10K | R-US_0204/5 | 0204/5 | RESISTOR, American symbol | 茶黒橙金 | 103 | タクマン | RD25SJ10K |  | 6AJS-7UJ6 |  |  |  | 1.6
R2 | 10K | R-US_0204/5 | 0204/5 | RESISTOR, American symbol | 茶黒橙金 | 103 | タクマン | RD25SJ10K |  | 6AJS-7UJ6 |  |  |  | 1.6
R3 | 330R | R-US_0204/5 | 0204/5 | RESISTOR, American symbol | 橙橙茶金 | 331 | タクマン | RD25SJ330R |  | 8A8S-7UJV |  |  |  | 1.6
R4 | 330R | R-US_0204/5 | 0204/5 | RESISTOR, American symbol | 橙橙茶金 | 331 | タクマン | RD25SJ300R |  | 8A8S-7UJV |  |  |  | 1.6
R5 | 240R | R-US_0204/5 | 0204/5 | RESISTOR, American symbol | 赤黄茶金 | 241 | タクマン | RD25SJ 240R |  | 2A8S-6UJM |  |  |  | 1.6
R6 | 10K | R-US_0204/5 | 0204/5 | RESISTOR, American symbol | 茶黒橙金 | 103 | タクマン | RD25SJ10K |  | 6AJS-7UJ6 |  |  |  | 1.6
R7 | 10K | R-US_0204/5 | 0204/5 | RESISTOR, American symbol | 茶黒橙金 | 103 | タクマン | RD25SJ10K |  | 6AJS-7UJ6 |  |  |  | 1.6
R8 | 10K | R-US_0204/5 | 0204/5 | RESISTOR, American symbol | 茶黒橙金 | 103 | タクマン | RD25SJ10K |  | 6AJS-7UJ6 |  |  |  | 1.6
R9 | 0R | R-US_0204/5 | 0204/5 | RESISTOR, American symbol | 黒 | 0 | タクマン | RD25SP 0R |  | 3ATS-7FJM |  |  |  | 1.6
R10 | 10K | R-US_0204/5 | 0204/5 | RESISTOR, American symbol | 茶黒橙金 | 103 | タクマン | RD25SJ10K |  | 6AJS-7UJ6 |  |  |  | 1.6
SP1 |  | PKM13EPYH4000 | PKM13EPYH4000 | SPEAKER |  |  | muRata | PKM13EPYH4000 | P-04118 |  |  |  |  | 30
SW1 | RESET | TVBP06 | TVBP06 | 2pin switch. | 黒 |  | Zhejiang Jianfu Electronics Co., Ltd | TVBP06-B043CB-B | P-08073 |  |  |  |  | 20
U1 | ESP-WROOM-02F | ESP-WROOM-02F | FRONT-FACE | WiFi module - ESP-WROOM-02 |  |  | Espressif | ESP-WROOM-02 | M-9607 | EEHD-4SH8 | 2346 |  |  | 550
U2 | TA48M033FS | TA48M033FS | HSIP3 | TA48 series |  |  | 株式会社東芝セミコンダクター社(TOSHIBA) | TA48M033F(S Q) | I-00538 |  |  |  | HSIP3 | 100
U3 | MCP4726A0T-E/CH | MCP4726A0T-E/CH | SOT95P270X145-6N | 12-Bit Digital-to-Analog Converter with EEPROM |  |  | Microchip | MCP4725A0T-E/CH | I-07611 |  |  |  | SOT-23-6 | 90
U4 | TCM809R | TCM809 | SOT23B-3 | POWER SUPPLY MONITOR |  |  | MICROCHIP | TCM809RVNB | I-02533 |  |  |  |  | 25
VR1 | 5K | 3362P | 3362P | 3362 Series |  |  | bourns | 3362P-1-502LF | P-03275 |  |  |  |  | 40
GOLD_ORB_SM1 | OSHWLOGOLOGO5MM | OSHWLOGOLOGO5MM | OSHW_5MM | The OSHW logo for PCB layout |  |  |  |  |  |  |  |  |  | 0
PCB1 | PCB_DP_RECTANGLE-37X60 | PCB_DP_RECTANGLE-37X60 | DP6037_V1 | Dangerous Prototypes Standard Rectangular PCB sizes |  |  | PCBGOGO | B67668AS3 60 x 37 |  |  |  |  |  | 540.79999999999995
 |  |  |  | 照光式押ボタン薄型Φ60円形・赤【LED白・旧式ランプホルダ】 |  |  | 三和電子 | OBSA-60UM-R-1F194 |  | EEHD-4JZS |  | 42784 |  | 2709
 |  |  |  | ワンタッチランプホルダー用ハーネス |  |  | 三和電子 | LHS-H |  | EEHD-4HXU |  |  |  | 210
 |  |  |  | XHコネクタ コンタクト(10個入)【SXH-001T-0.6*10】 |  |  | 日本圧着端子製造(JST) | SXH-001T-0.6*10 |  |  |  | 59201 |  | 180
 |  |  |  | 長方形コネクタ-ハウジング【XHP-4】 |  |  | 日本圧着端子製造(JST) | XHP-4 |  |  |  | 14896331 |  | 40
 |  |  |  | ケース（未定）ミテイ

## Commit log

2017-07-02 Initial
2017-07-02 Add PDF
2017-07-02 Add PDF
    Add PDF
2017-08-29 Lib3 Initial
2017-08-29 Delete

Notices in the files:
parts and their libraries:
SparkFun-Connectors: Licensing: Creative Commons ShareAlike 4.0 International - https://creativecommons.org/licenses/by-sa/4.0
microbuilder: This work is placed in the public domain, and may be freely used for commercial and non-commercial work with the following conditions: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
